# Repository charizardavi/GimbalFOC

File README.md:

# GimbalFOC

## Sponsored By

A gimbal BLDC controller:
- MCU: ESP32-S3 (XIAO)
- Motor Controller: DRV8813

## Other Parts
- [BLDC](https://shop.iflight.com/gimbal-motors-cat44/ipower-motor-gm4108h-120t-brushless-gimbal-motor-pro217)
- Battery: Tested with 4S LiPO

## Completed
- V1
- V2 (much smaller PCB, addition of ESP32S3)

## TODO
- Build and test 3-axis

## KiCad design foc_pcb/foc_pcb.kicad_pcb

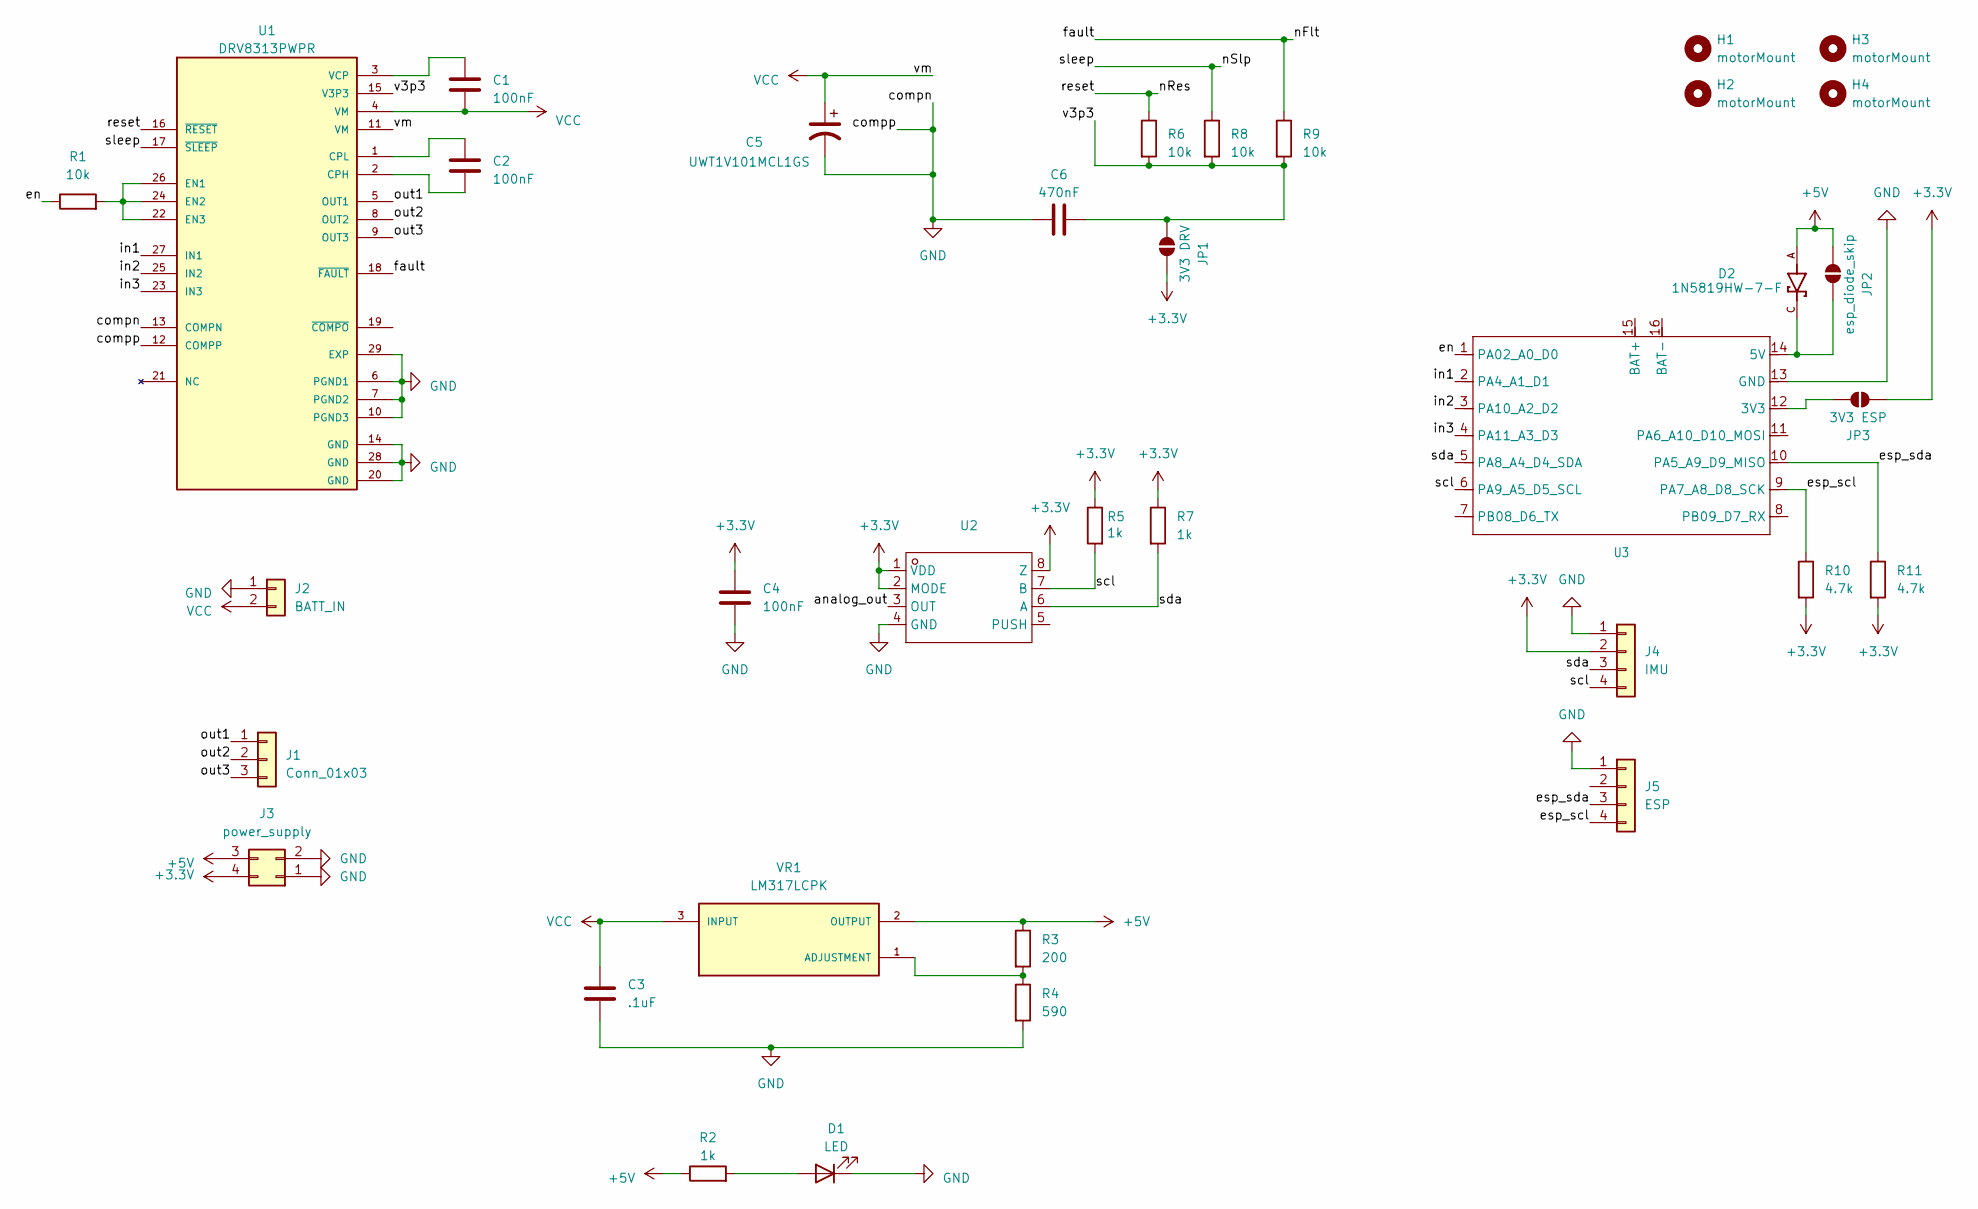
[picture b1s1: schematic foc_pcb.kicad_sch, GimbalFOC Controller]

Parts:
C1, C2, C4: 100nF; C_0603_1608Metric
C3: .1uF; C_0603_1608Metric
C5: UWT1V101MCL1GS; PCAP_6.3x7.7-ELECT_NCA-L
C6: 470nF; C_0603_1608Metric
D1: LED; LED_0603_1608Metric
D2: 1N5819HW-7-F; SOD3715X145N; PARTREV 18-2
H1, H2, H3, H4: motorMount; MountingHole_3.2mm_M3
J1: Conn_01x03; PinHeader_1x03_P2.54mm_Vertical
J2: BATT_IN; JST_VH_B2P-VH_1x02_P3.96mm_Vertical
J3: power_supply; PinHeader_2x02_P2.54mm_Vertical
J4: IMU; PinHeader_1x04_P2.00mm_Vertical
J5: ESP; PinHeader_1x04_P2.00mm_Vertical
JP1: 3V3 DRV; SolderJumper-2_P1.3mm_Open_TrianglePad1.0x1.5mm
JP2: esp_diode_skip; SolderJumper-2_P1.3mm_Open_TrianglePad1.0x1.5mm
JP3: 3V3 ESP; SolderJumper-2_P1.3mm_Open_TrianglePad1.0x1.5mm
R1, R6, R8, R9: 10k; R_0603_1608Metric
R2, R5, R7: 1k; R_0603_1608Metric
R3: 200; R_0603_1608Metric
R4: 590; R_0603_1608Metric
R10, R11: 4.7k; R_0603_1608Metric
U1: DRV8313PWPR; HTSSOP-28_L9.8-W4.5-P0.65-LS6.6-BL-EP; PARTREV D; DigiKey_Part_Number 296-40072-2-ND
U2: SOP-8_L4.9-W3.9-P1.27-LS6.0-BL; Manufacturer Part MT6701CT-STD; LCSC Part Name 霍尔在线编程角度位置传感器
U3: MOUDLE14P-SMD-2.54-21X17.8MM
VR1: LM317LCPK; VREG_LM317LCPK; PARTREV E; DigiKey_Part_Number 296-26093-2-ND

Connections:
+3.3V: C4.2, J3.4, J4.2, JP1.1 (A), JP3.2 (B), R5.1, R7.1, R10.2, R11.2, U2.1 (VDD), U2.2 (MODE), U2.8 (Z)
+5V: D2.A, J3.3, JP2.2 (B), R2.1, R3.1, VR1.2 (OUTPUT)
/analog_out: U2.3 (OUT)
/en: R1.1, U3.1 (PA02_A0_D0)
/esp_scl: J5.4, R10.1, U3.9 (PA7_A8_D8_SCK)
/esp_sda: J5.3, R11.1, U3.10 (PA5_A9_D9_MISO)
/fault: R9.1, U1.18 (~FAULT)
/in1: U1.27 (IN1), U3.2 (PA4_A1_D1)
/in2: U1.25 (IN2), U3.3 (PA10_A2_D2)
/in3: U1.23 (IN3), U3.4 (PA11_A3_D3)
/nRes: R6.1, U1.16 (~RESET)
/nSlp: R8.1, U1.17 (~SLEEP)
/out1: J1.1, U1.5 (OUT1)
/out2: J1.2, U1.8 (OUT2)
/out3: J1.3, U1.9 (OUT3)
/scl: J4.4, R5.2, U2.7 (B), U3.6 (PA9_A5_D5_SCL)
/sda: J4.3, R7.2, U2.6 (A), U3.5 (PA8_A4_D4_SDA)
/v3p3: C6.2, JP1.2 (B), R6.2, R8.2, R9.2, U1.15 (V3P3)
GND: C3.2, C4.1, C5.2, C6.1, D1.1 (K), J2.1, J3.1, J3.2, J4.1, J5.1, R4.2, U1.6 (PGND1), U1.7 (PGND2), U1.10 (PGND3), U1.12 (COMPP), U1.13 (COMPN), U1.14 (GND), U1.20 (GND), U1.28 (GND), U1.29 (EXP), U2.4 (GND), U3.13 (GND)
unnamed: D1.2 (A), R2.2
unnamed: D2.C, JP2.1 (A), U3.14 (5V)
unnamed: JP3.1 (A), U3.12 (3V3)
unnamed: C2.2, U1.2 (CPH)
unnamed: C2.1, U1.1 (CPL)
unnamed: R1.2, U1.22 (EN3), U1.24 (EN2), U1.26 (EN1)
unnamed: C1.1, U1.3 (VCP)
unnamed: R3.2, R4.1, VR1.1 (ADJUSTMENT)
VCC: C1.2, C3.1, C5.1, J2.2, U1.4 (VM), U1.11 (VM), VR1.3 (INPUT)

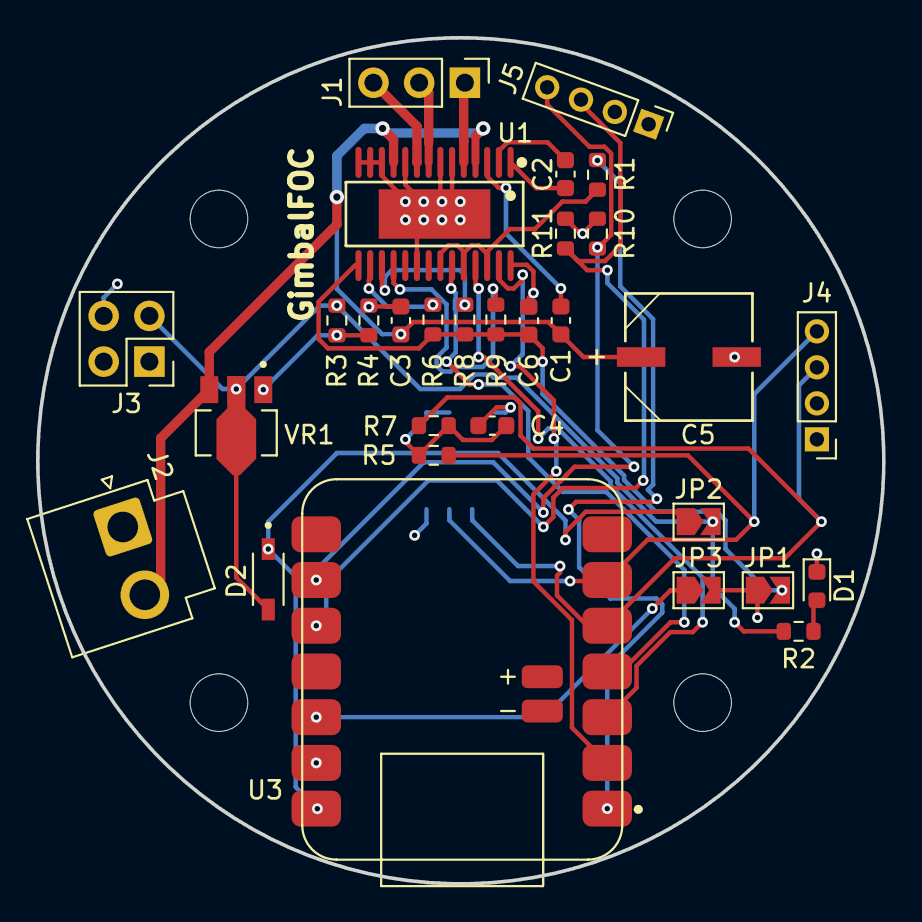
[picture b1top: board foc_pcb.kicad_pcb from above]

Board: 4 copper layers, 47.0 x 47.0 mm, 35 parts (1 on the bottom side), 27 nets.

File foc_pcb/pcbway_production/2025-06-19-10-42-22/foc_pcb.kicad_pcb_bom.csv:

Designator,Quantity,Value,Footprint,Package,MPN,DNP,Mount_Type,Description,MF,Purchase-URL,Check_prices,STANDARD,PARTREV,SnapEDA_Link,MP,Description_1,MANUFACTURER,DigiKey_Part_Number,SNAPEDA_PACKAGE_ID,MAXIMUM_PACKAGE_HEIGHT,Manufacturer Part,Manufacturer,Supplier Part,Supplier,LCSC Part Name
"C1, C2, C4",3,100nF,C_0603_1608Metric,,,,smt,Unpolarized capacitor,,,,,,,,,,,,,,,,,
C3,1,.1uF,C_0603_1608Metric,,,,smt,Unpolarized capacitor,,,,,,,,,,,,,,,,,
C5,1,UWT1V101MCL1GS,PCAP_6.3x7.7-ELECT_NCA-L,,,,smt,"Polarized capacitor, US symbol",,,,,,,,,,,,,,,,,
C6,1,470nF,C_0603_1608Metric,,,,smt,Unpolarized capacitor,,,,,,,,,,,,,,,,,
D1,1,LED,LED_0603_1608Metric,,,,smt,Light emitting diode,,,,,,,,,,,,,,,,,
D2,1,1N5819HW-7-F,SOD3715X145N,None,,,smt,,Diodes Zetex,https://www.snapeda.com/api/url_track_click_mouser/?unipart_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 Zetex&part_name=1N5819HW-7-F&search_term=None,https://www.snapeda.com/parts/1N5819HW-7-F/Zetex/view-part/?ref=eda,IPC-7351B,18-2,https://www.snapeda.com/parts/1N5819HW-7-F/Zetex/view-part/?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,1N5819HW-7-F,"
Diode Schottky 40V 1A 2-Pin SOD-123 T/R
",Diodes Inc.,,,,,,,,
J1,1,Conn_01x03,PinHeader_1x03_P2.54mm_Vertical,,,,tht,"Generic connector, single row, 01x03, script generated (kicad-library-utils/schlib/autogen/connector/)",,,,,,,,,,,,,,,,,
J2,1,BATT_IN,JST_VH_B2P-VH_1x02_P3.96mm_Vertical,,,,tht,"Generic connector, single row, 01x02, script generated (kicad-library-utils/schlib/autogen/connector/)",,,,,,,,,,,,,,,,,
J3,1,power_supply,PinHeader_2x02_P2.54mm_Vertical,,,,tht,"Generic connector, double row, 02x02, counter clockwise pin numbering scheme (similar to DIP package numbering), script generated (kicad-library-utils/schlib/autogen/connector/)",,,,,,,,,,,,,,,,,
J4,1,IMU,PinHeader_1x04_P2.00mm_Vertical,,,,tht,"Generic connector, single row, 01x04, script generated (kicad-library-utils/schlib/autogen/connector/)",,,,,,,,,,,,,,,,,
J5,1,ESP,PinHeader_1x04_P2.00mm_Vertical,,,,tht,"Generic connector, single row, 01x04, script generated (kicad-library-utils/schlib/autogen/connector/)",,,,,,,,,,,,,,,,,
"R1, R6, R8, R9",4,10k,R_0603_1608Metric,,,,smt,Resistor,,,,,,,,,,,,,,,,,
"R10, R11",2,4.7k,R_0603_1608Metric,,,,smt,Resistor,,,,,,,,,,,,,,,,,
"R2, R5, R7",3,1k,R_0603_1608Metric,,,,smt,Resistor,,,,,,,,,,,,,,,,,
R3,1,200,R_0603_1608Metric,,,,smt,Resistor,,,,,,,,,,,,,,,,,
R4,1,590,R_0603_1608Metric,,,,smt,Resistor,,,,,,,,,,,,,,,,,
U1,1,DRV8313PWPR,HTSSOP-28_L9.8-W4.5-P0.65-LS6.6-BL-EP,HTSSOP-28 Texas Instruments,,,tht,65-V max 3-A peak 3-phase motor driver with integrated FETs,Texas Instruments,,https://www.snapeda.com/parts/DRV8313PWPR/Texas+Instruments/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,Manufacturer Recommendations,D,https://www.snapeda.com/parts/DRV8313PWPR/Texas+Instruments/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,DRV8313PWPR,,Texas Instruments,296-40072-2-ND,102627,1.2 mm,,,,,
U2,1,~,SOP-8_L4.9-W3.9-P1.27-LS6.0-BL,,,,tht,,,,,,,,,,,,,,MT6701CT-STD,MagnTek(麦歌恩),C2856764,LCSC,霍尔在线编程角度位置传感器
U3,1,~,MOUDLE14P-SMD-2.54-21X17.8MM,,,,tht,,,,,,,,,,,,,,,,,,
VR1,1,LM317LCPK,VREG_LM317LCPK,SOT-89-3 Texas Instruments,,,smt,,Texas Instruments,https://www.snapeda.com/api/url_track_click_mouser/?unipart_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 Instruments&part_name=LM317LCPK&search_term=None,https://www.snapeda.com/parts/LM317LCPK/Texas+Instruments/vi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,Manufacturer Recommendations,E,https://www.snapeda.com/parts/LM317LCPK/Texas+Instruments/vi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,LM317LCPK,"
100-mA, 35-V, adjustable linear voltage regulator
",Texas Instruments,296-26093-2-ND,102648,1.6 mm,,,,,

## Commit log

2024-08-03 schema v1 done
2024-08-03 added power connectors, temp commit for 8.0 migration
2024-08-04 migrated, saving old lm2596
2024-08-04 added todo
2024-08-04 fixed readme formatting
2024-08-05 fixed regulator, schema done (?)
2024-08-05 fixed readme again
2024-08-05 added motor mount
2024-08-07 added level shifter, layout done
2024-08-07 updated todo
2024-08-08 backup in case footprint swap fails
2024-08-08 swapped footprint, fixed several DRC violations
2024-08-10 added thicker tracks for vcc
2024-08-11 before switch usb
2024-08-11 reverted to old usb, pray to jlc gods
2024-08-12 board v1 done, to be ordered soon
2024-08-22 readme updated
2024-08-26 added test scripts, as5600 working, drv tbd
2024-10-30 foc code done, pre-redesign
2024-10-31 V2 redesign done, needs review
2024-10-31 fixes parts lib folder hopefully
2024-11-01 compacted layout, finished V2
2024-11-13 fixed some drc and added silkscreen
2024-11-29 v1 assembled and firmware completed, some PID tuning required
2024-12-08 added kicad preview
2024-12-08 fixed kicad preview
2025-03-19 V2 FOC and SPI working
2025-03-21 V2 final commit
2025-03-21 V3 Intial Commit
2025-03-22 readme update
2025-03-26 temp commit before re-layout
2025-04-01 removed rendunant solder jumpers
2025-07-07 v3 incoming
2025-07-13 open loop works
2025-08-08 fix readme, add tests
2025-08-08 fixed the readme again
2025-08-08 added sponsor
